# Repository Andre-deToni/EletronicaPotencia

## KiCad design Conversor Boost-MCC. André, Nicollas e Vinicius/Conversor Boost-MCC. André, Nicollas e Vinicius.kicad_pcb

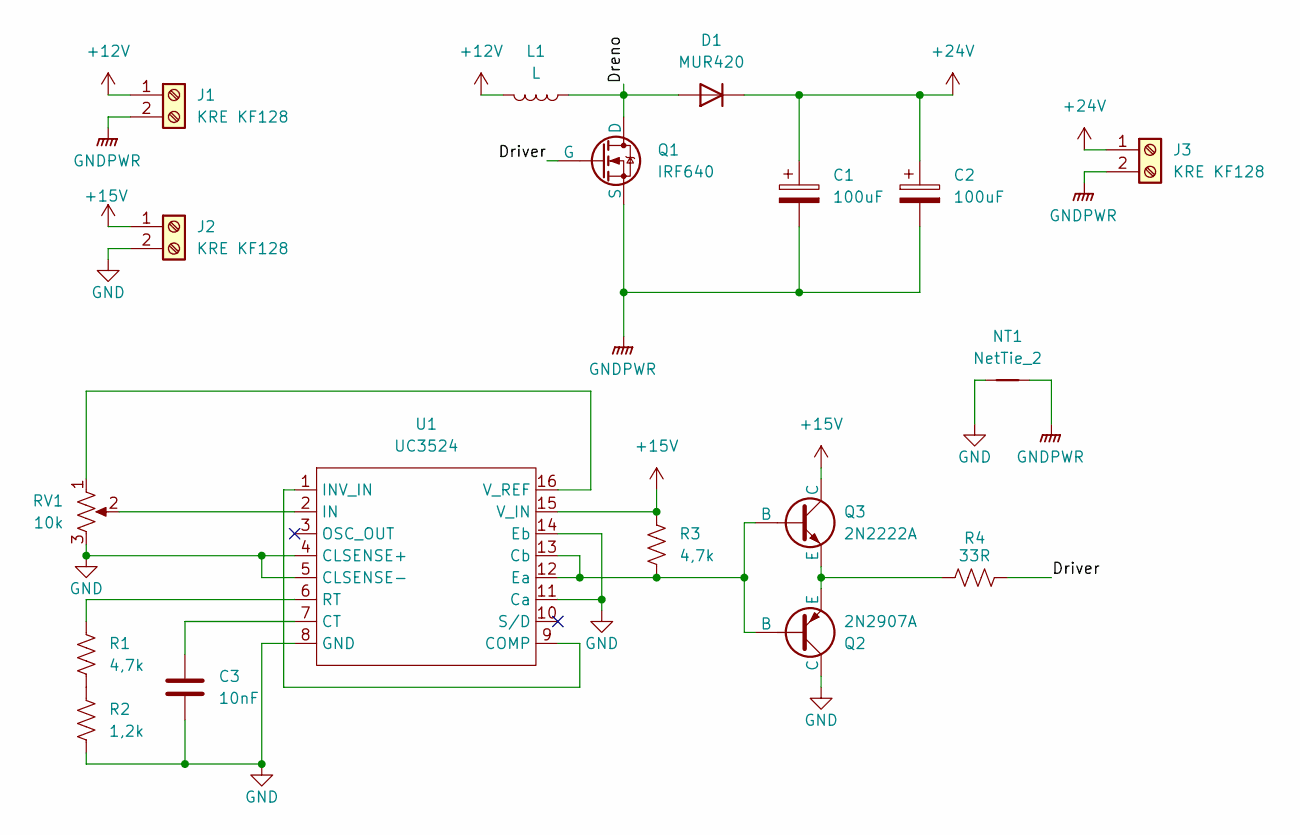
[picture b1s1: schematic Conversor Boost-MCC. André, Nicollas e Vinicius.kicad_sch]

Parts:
C1, C2: 100uF; CP_Radial_D8.0mm_P5.00mm
C3: 10nF; C_Rect_L7.0mm_W2.0mm_P5.00mm
D1: MUR420
J1, J2, J3: KRE KF128; KF128 2 VIAS
L1: L; Indutor_Potência
NT1: NetTie_2; NetTie-2_SMD_Pad2.0mm
Q1: IRF640; TO-220
Q2: 2N2907A; TO-92_Inline_Wide
Q3: 2N2222A; TO-92_Inline_Wide
R1, R3: 4,7k; R_Axial_DIN0207_L6.3mm_D2.5mm_P10.16mm_Horizontal
R2: 1,2k; R_Axial_DIN0207_L6.3mm_D2.5mm_P10.16mm_Horizontal
R4: 33R; R_Axial_DIN0207_L6.3mm_D2.5mm_P10.16mm_Horizontal
RV1: 10k; Potentiometer_Bourns_3296W_Vertical
U1: UC3524; DIP-16_W7.62mm_Socket

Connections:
+12V: J1.1, L1.2
+15V: J2.1, Q3.1 (C), R3.1, U1.15 (V_IN)
+24V: C1.1, C2.1, D1.1 (K), J3.1
/Dreno: D1.2 (A), L1.1, Q1.1 (D)
/Driver: Q1.2 (G), R4.2
GND: C3.2, J2.2, NT1.1, Q2.1 (C), R2.2, RV1.3, U1.4 (CLSENSE+), U1.5 (CLSENSE-), U1.8 (GND), U1.11 (Ca), U1.14 (Eb)
GNDPWR: C1.2, C2.2, J1.2, J3.2, NT1.2, Q1.3 (S)
unnamed: Q2.2 (B), Q3.2 (B), R3.2, U1.12 (Ea), U1.13 (Cb)
unnamed: Q2.3 (E), Q3.3 (E), R4.1
unnamed: R1.2, R2.1
unnamed: U1.1 (INV_IN), U1.9 (COMP)
unnamed: C3.1, U1.7 (CT)
unnamed: RV1.2, U1.2 (IN)
unnamed: R1.1, U1.6 (RT)
unnamed: RV1.1, U1.16 (V_REF)

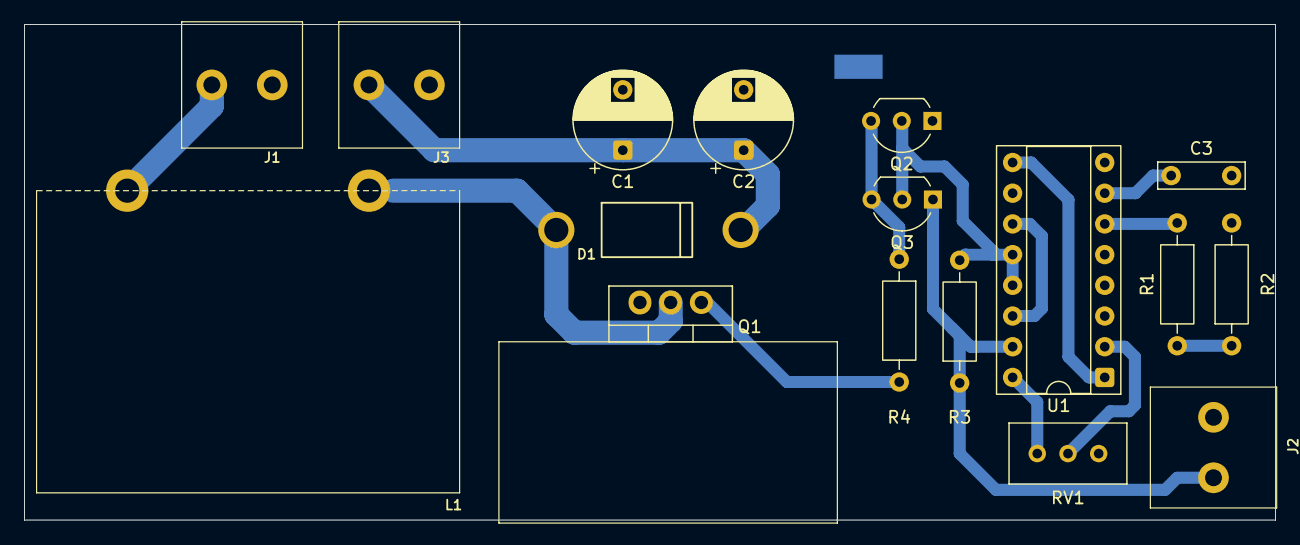
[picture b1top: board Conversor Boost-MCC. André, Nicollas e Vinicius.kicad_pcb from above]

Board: 2 copper layers, 103.5 x 41.0 mm, 18 parts (1 on the bottom side), 15 nets.

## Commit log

2025-11-24 Layout finalizado; Footprints inseridas (exceto indutor)
2025-11-25 Layout finalizado
2025-11-25 Arquivos Gerbers gerados
